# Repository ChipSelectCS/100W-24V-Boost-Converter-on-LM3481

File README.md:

# 100W-24V-Boost-Converter-on-LM3481

Great and powerful 100W Step up Converter. Provides and option to toggle the converter on and off using the onboard pins.

Open in KiCad

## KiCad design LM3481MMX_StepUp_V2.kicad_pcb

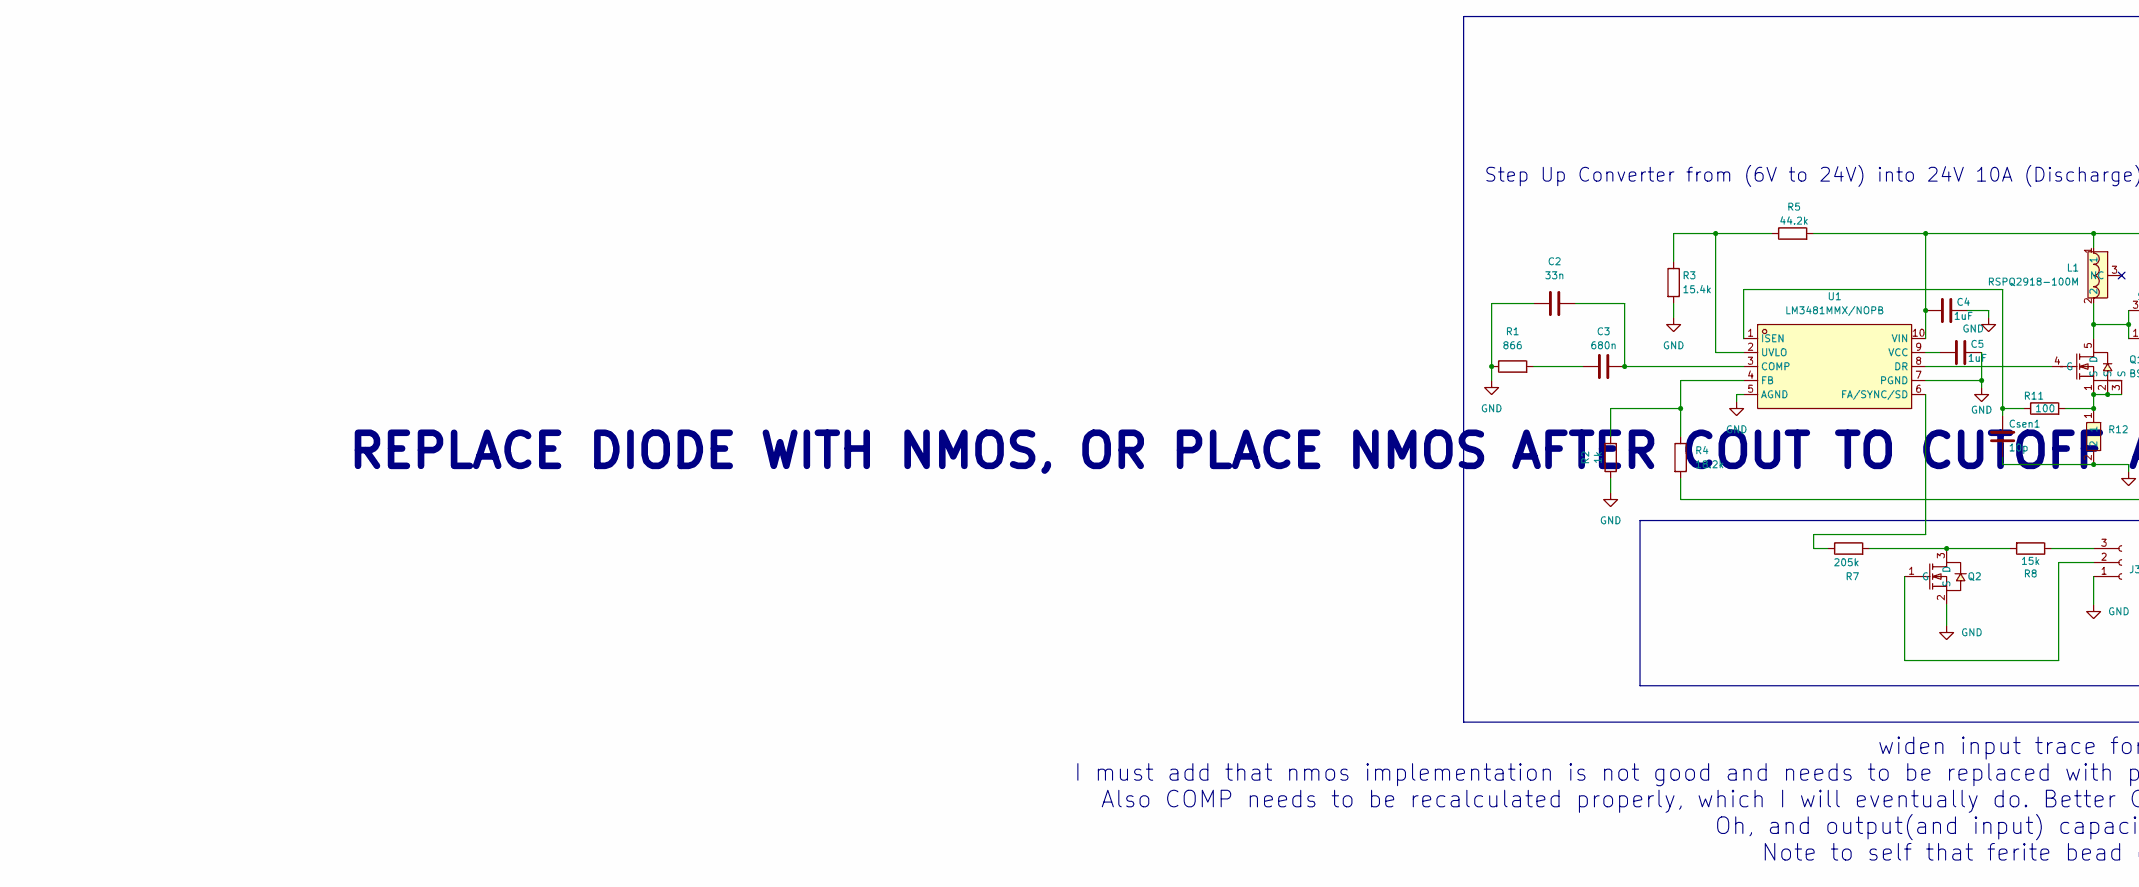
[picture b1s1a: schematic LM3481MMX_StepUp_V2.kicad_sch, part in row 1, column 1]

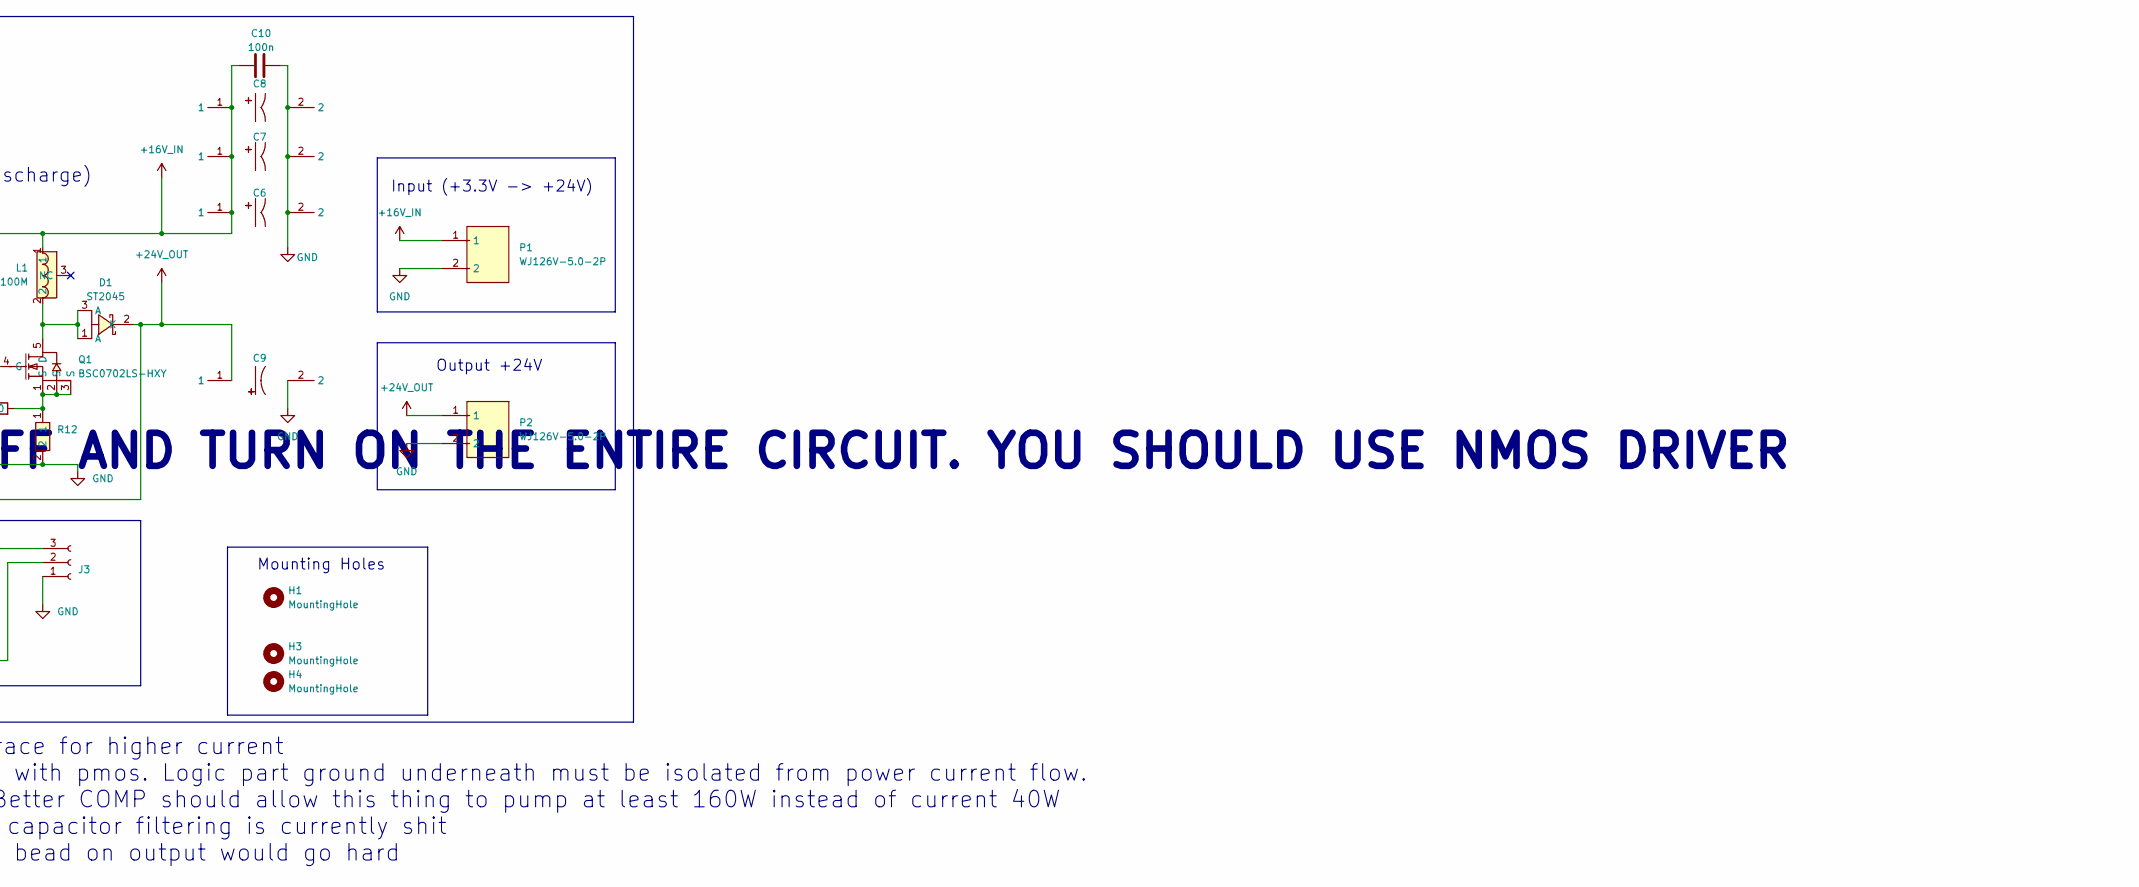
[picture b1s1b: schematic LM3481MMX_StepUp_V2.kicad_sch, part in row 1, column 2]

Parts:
C2: 33n; C_0603_1608Metric
C3: 680n; C_0603_1608Metric
C4, C5: 1uF; C_0603_1608Metric
C6, C7, C8: HV1H227M1010PZ; CAP-SMD_BD10.0-L10.3-W10.3-LS11.3-FD; LCSC Part C5246564
C9: OVZ121M1V1013-TRO; CAP-SMD_BD10.0-L10.4-W10.4-LS11.0-FD; LCSC Part C250089
C10: 100n; C_0603_1608Metric
Csen1: 10p; C_0603_1608Metric
D1: ST2045; TO-277_3P-L5.4-W4.0-LS6.5-BR; LCSC Part C840773
H1, H3, H4: MountingHole; MountingHole_2.2mm_M2
J3: Conn_01x03_Socket; PinSocket_1x03_P2.54mm_Vertical
L1: RSPQ2918-100M; IND-SMD_3P-L27.9-W19.7-P10.43-LS27.9-BL-A; LCSC Part C32712982
P1, P2: WJ126V-5.0-2P; CONN-TH_WJ126V-5.0-2P; LCSC Part C8404
Q1: BSC0702LS-HXY; TDSON-8_L5.9-W5.2-P1.27-BL; LCSC Part C20606289
Q2: 2N7002K_C414015; SOT-23-3_L2.9-W1.3-P1.90-LS2.4-BR; LCSC Part C414015
R1: 866; R_0603_1608Metric
R2: 1k; R_0603_1608Metric
R3: 15.4k; R_0603_1608Metric
R4: 18.2k; R_0603_1608Metric
R5: 44.2k; R_0603_1608Metric
R7: 205k; R_0603_1608Metric
R8: 15k; R_0603_1608Metric
R11: 100; R_0603_1608Metric
R12: FRM252WFR0025TN; R2512; LCSC Part C7420002
U1: LM3481MMX/NOPB; VSSOP-10_L3.0-W3.0-P0.50-LS4.9-BL; LCSC Part C543002

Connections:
+16V_IN: C4.1, C6.1, C7.1, C8.1, C10.2, L1.1, P1.1, R5.2, U1.10 (VIN)
+24V_OUT: C9.1, D1.2 (K), P2.1, R4.2
GND: C2.1, C4.2, C5.2, C6.2, C7.2, C8.2, C9.2, C10.1, Csen1.1, J3.1, P1.2, P2.2, Q2.2 (S), R1.1, R2.1, R3.2, R12.2, U1.5 (AGND), U1.7 (PGND)
unnamed: C3.1, R1.2
unnamed: J3.2, Q2.1 (G)
unnamed: J3.3, R8.1
unnamed: D1.1 (A), D1.3 (A), L1.2, Q1.5 (D)
unnamed: Q1.4 (G), U1.8 (DR)
unnamed: Q1.1 (S), Q1.2 (S), Q1.3 (S), R11.2, R12.1
unnamed: Q2.3 (D), R7.2, R8.2
unnamed: C2.2, C3.2, U1.3 (COMP)
unnamed: R7.1, U1.6 (FA/SYNC/SD)
unnamed: R2.2, R4.1, U1.4 (FB)
unnamed: Csen1.2, R11.1, U1.1 (ISEN)
unnamed: R3.1, R5.1, U1.2 (UVLO)
unnamed: C5.1, U1.9 (VCC)

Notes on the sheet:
REPLACE DIODE WITH NMOS, OR PLACE NMOS AFTER COUT TO CUTOFF AND TURN ON THE ENTIRE CIRCUIT. YOU SHOULD USE NMOS DRIVER
widen input trace for higher current I must add that nmos implementation is not good and needs to be replaced with pmos. Logic part ground underneath must be isolated from power current flow. Also COMP needs to be recalculated properly, which I will eventually do. Better COMP should allow this thin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
Input (+3.3V -> +24V)
Step Up Converter from (6V to 24V) into 24V 10A (Discharge)
Output +24V
Mounting Holes

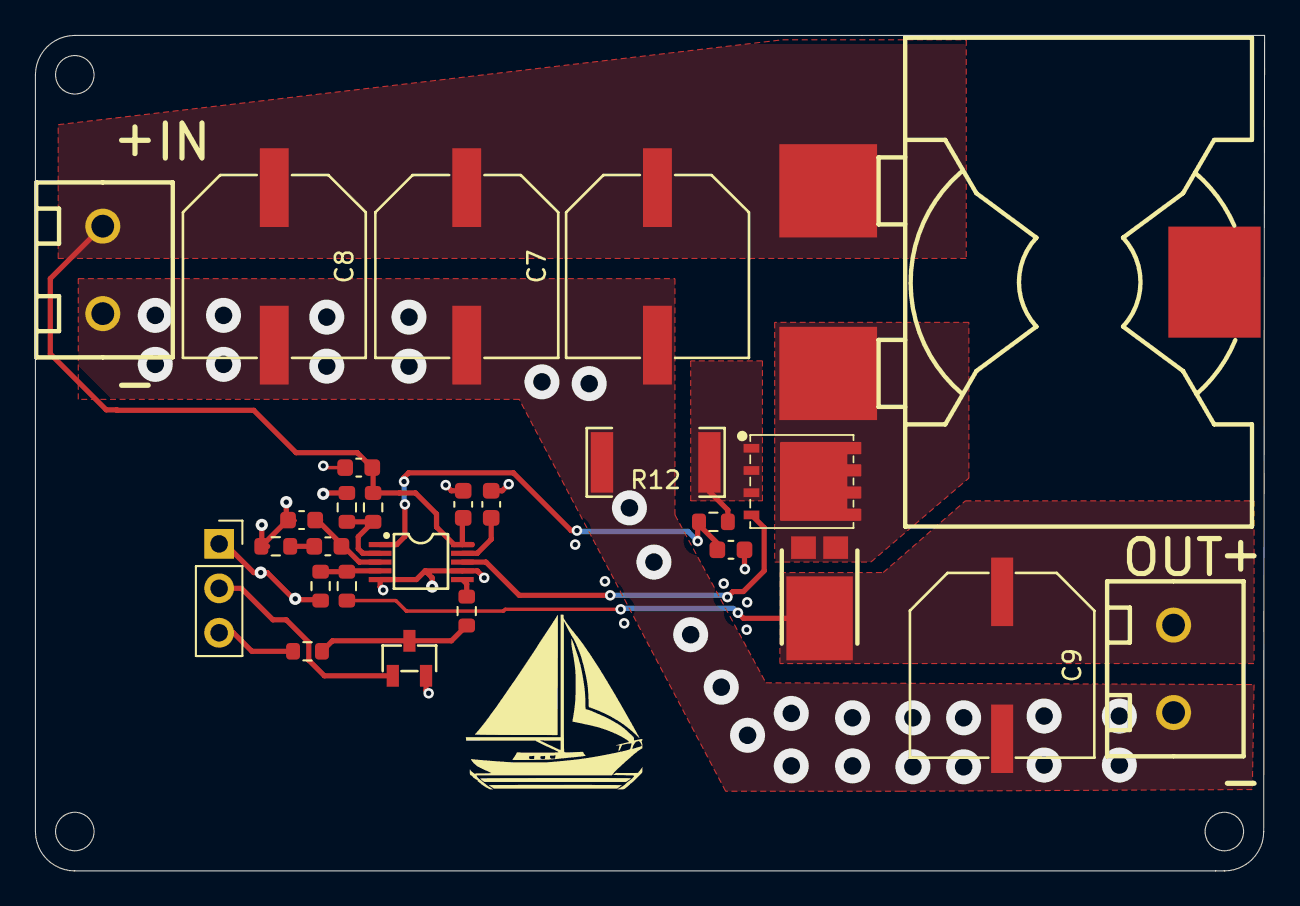
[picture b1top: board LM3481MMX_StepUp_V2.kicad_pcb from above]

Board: 2 copper layers, 70.3 x 47.8 mm, 30 parts (0 on the bottom side), 16 nets.

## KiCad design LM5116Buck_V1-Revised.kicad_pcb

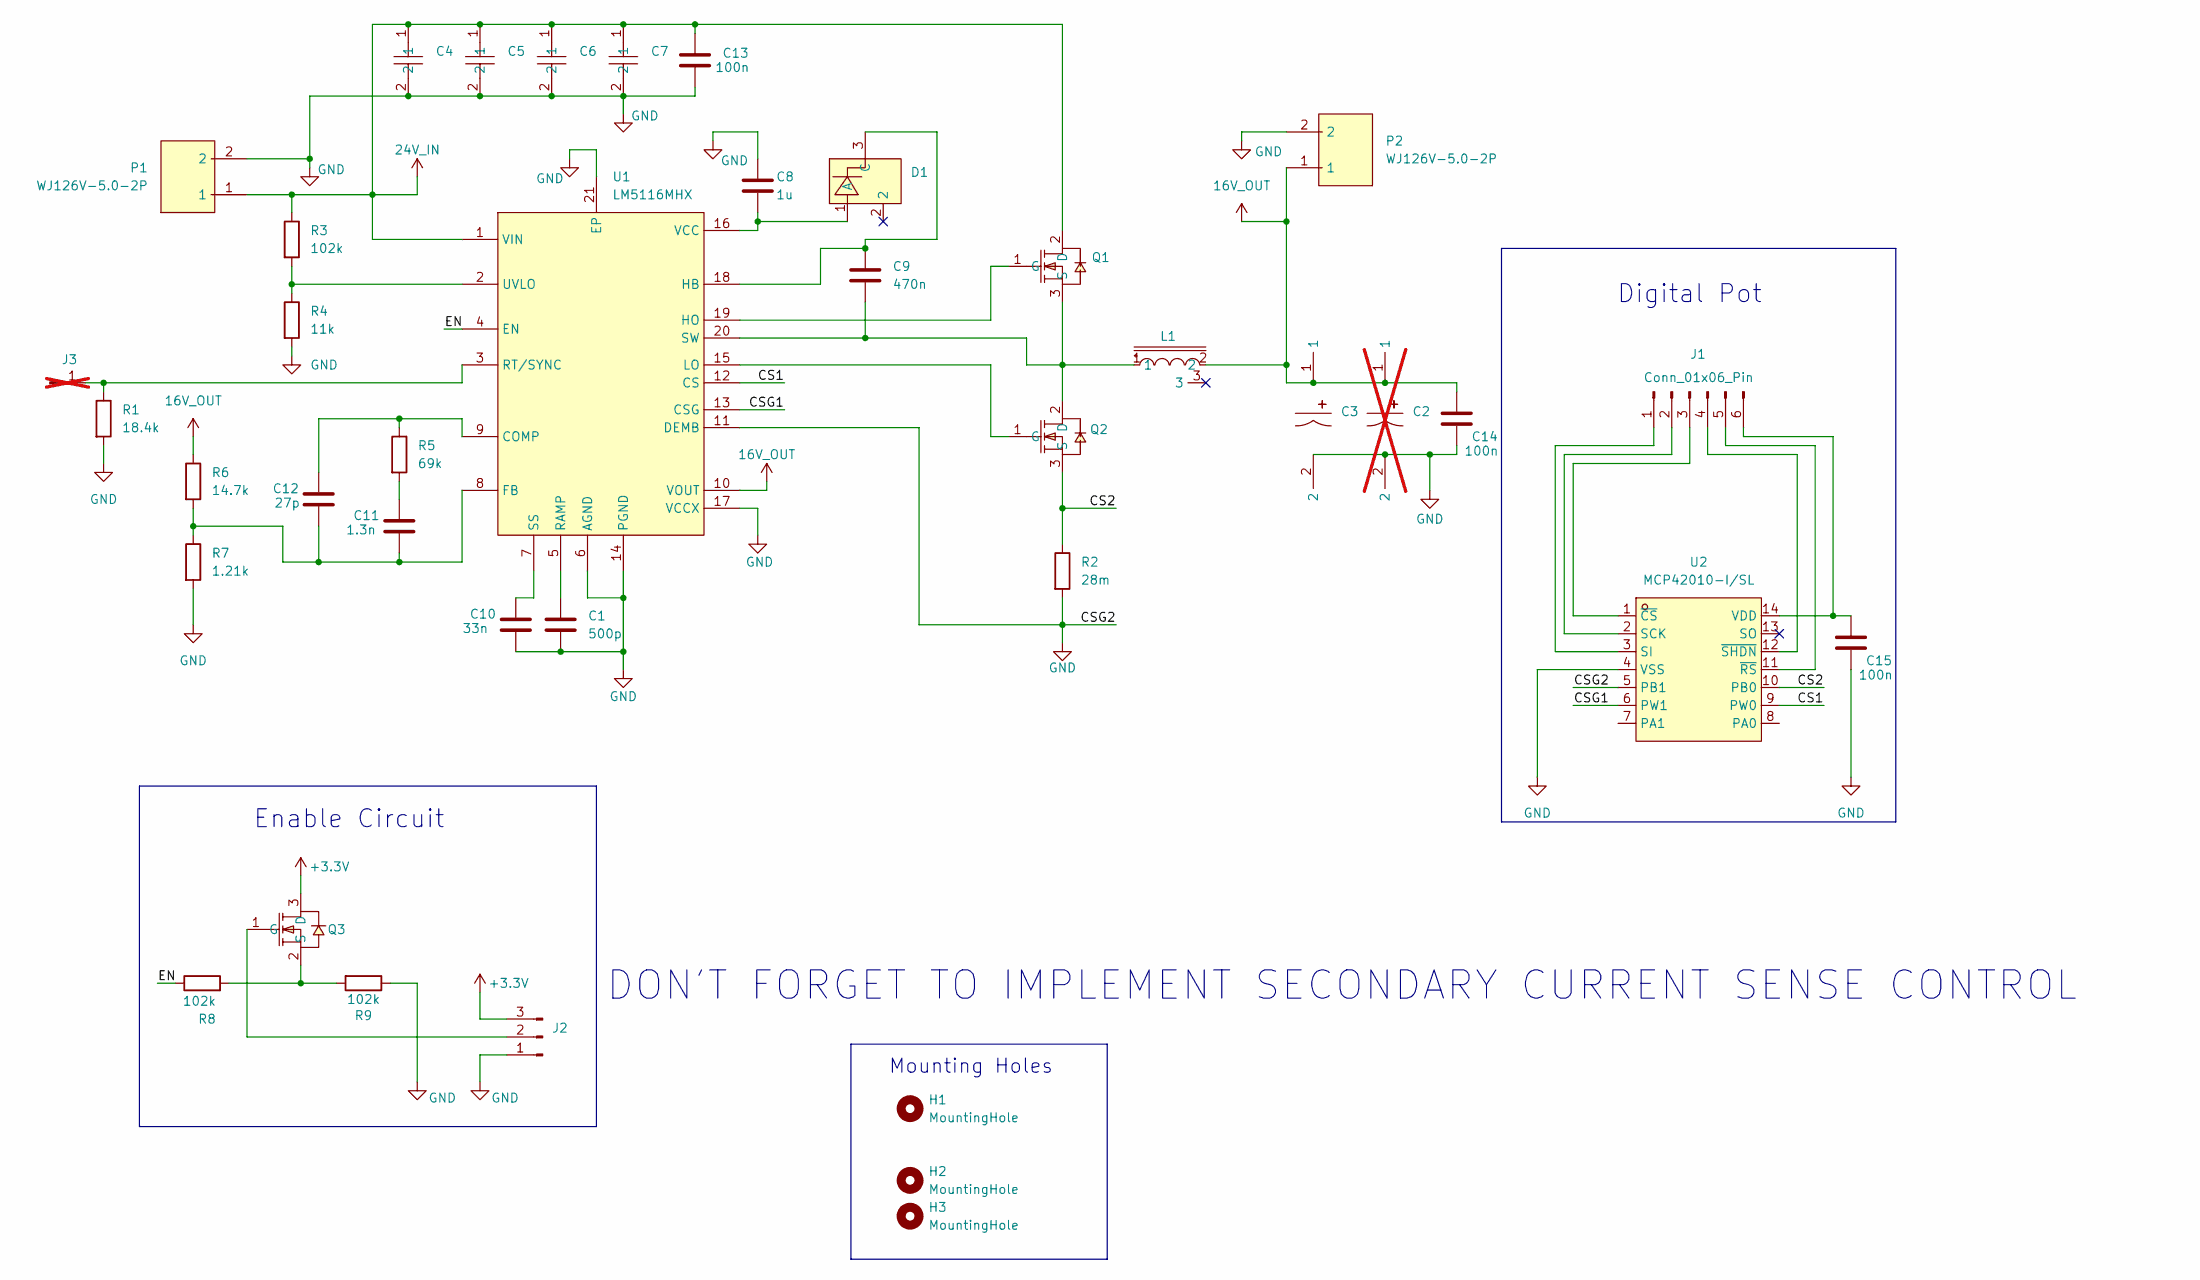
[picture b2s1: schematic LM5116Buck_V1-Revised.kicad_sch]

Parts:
C1: 500p; C_0603_1608Metric
C2: HV1H227M1010PZ; CAP-SMD_BD10.0-L10.3-W10.3-LS11.3-FD; LCSC Part C5246564; not fitted
C3: HV1H227M1010PZ; CAP-SMD_BD10.0-L10.3-W10.3-LS11.3-FD; LCSC Part C5246564
C4, C5, C6, C7: FS32X225K101EGG; C1210; LCSC Part C153036
C8: 1u; C_0603_1608Metric
C9: 470n; C_0603_1608Metric
C10: 33n; C_0603_1608Metric
C11: 1.3n; C_0603_1608Metric
C12: 27p; C_0603_1608Metric
C13, C14, C15: 100n; C_0603_1608Metric
D1: BAS20LT1G; SOT-23-3_L2.9-W1.3-P1.90-LS2.4-BL-1; LCSC Part C232529
H1, H2, H3: MountingHole; MountingHole_2.2mm_M2
J1: Conn_01x06_Pin; PinHeader_1x06_P2.54mm_Vertical
J2: Conn_01x03_Pin; PinHeader_1x03_P2.54mm_Vertical
J3: Conn_01x01_Pin; PinHeader_1x01_P2.54mm_Vertical; not fitted
L1: FC-SE2918-220M; IND-SMD_3P-L27.9-W19.7-P10.43-LS27.9-BL-A; LCSC Part C2962789
P1, P2: WJ126V-5.0-2P; CONN-TH_WJ126V-5.0-2P; LCSC Part C8404
Q1, Q2: IRFR1205TRPBF-ES; TO-252-2_L6.6-W6.1-P4.57-LS9.9-BR-CW; LCSC Part C21713850
Q3: 2N7002K_C414015; SOT-23-3_L2.9-W1.3-P1.90-LS2.4-BR; LCSC Part C414015
R1: 18.4k; R_0603_1608Metric
R2: 28m; R_2512_6332Metric
R3, R8, R9: 102k; R_0603_1608Metric
R4: 11k; R_0603_1608Metric
R5: 69k; R_0603_1608Metric
R6: 14.7k; R_0603_1608Metric
R7: 1.21k; R_0603_1608Metric
U1: LM5116MHX; HTSSOP-20_L6.5-W4.4-P0.65-LS6.4-BL-EP; LCSC Part C13755
U2: MCP42010-I/SL; SOIC-14_L8.7-W3.9-P1.27-LS6.0-BL; LCSC Part C481366

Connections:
16V_OUT: C2.1, C3.1, C14.1, L1.2, P2.1, R6.1, U1.10 (VOUT)
24V_IN: C4.1, C5.1, C6.1, C7.1, C13.1, P1.1, Q1.2 (D), R3.1, U1.1 (VIN)
+3.3V: J2.3, Q3.3 (D)
/CS1: U1.12 (CS), U2.9 (PW0)
/CS2: Q2.3 (S), R2.1, U2.10 (PB0)
/CSG1: U1.13 (CSG), U2.6 (PW1)
/EN: R8.1, U1.4 (EN)
GND: C1.2, C2.2, C3.2, C4.2, C5.2, C6.2, C7.2, C8.1, C10.2, C13.2, C14.2, C15.2, J2.1, P1.2, P2.2, R1.2, R2.2, R4.2, R7.2, R9.1, U1.6 (AGND), U1.11 (DEMB), U1.14 (PGND), U1.17 (VCCX), U1.21 (EP), U1.GND, U2.4 (VSS), U2.5 (PB1)
unnamed: C11.1, R5.2
unnamed: C8.2, D1.1 (A), U1.16 (VCC)
unnamed: C9.1, D1.3 (C), U1.18 (HB)
unnamed: J1.1, U2.3 (SI)
unnamed: J1.2, U2.2 (SCK)
unnamed: J1.3, U2.1 (~CS)
unnamed: J1.4, U2.12 (~SHDN)
unnamed: J1.5, U2.11 (~RS)
unnamed: C15.1, J1.6, U2.14 (VDD)
unnamed: J2.2, Q3.1 (G)
unnamed: J3.1, R1.1, U1.3 (RT/SYNC)
unnamed: Q1.1 (G), U1.19 (HO)
unnamed: C9.2, L1.1, Q1.3 (S), Q2.2 (D), U1.20 (SW)
unnamed: Q2.1 (G), U1.15 (LO)
unnamed: Q3.2 (S), R8.2, R9.2
unnamed: C12.1, R5.1, U1.9 (COMP)
unnamed: C11.2, C12.2, R6.2, R7.1, U1.8 (FB)
unnamed: C1.1, U1.5 (RAMP)
unnamed: C10.1, U1.7 (SS)
unnamed: R3.2, R4.1, U1.2 (UVLO)

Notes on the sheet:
Enable Circuit
Digital Pot
DON'T FORGET TO IMPLEMENT SECONDARY CURRENT SENSE CONTROL
Mounting Holes

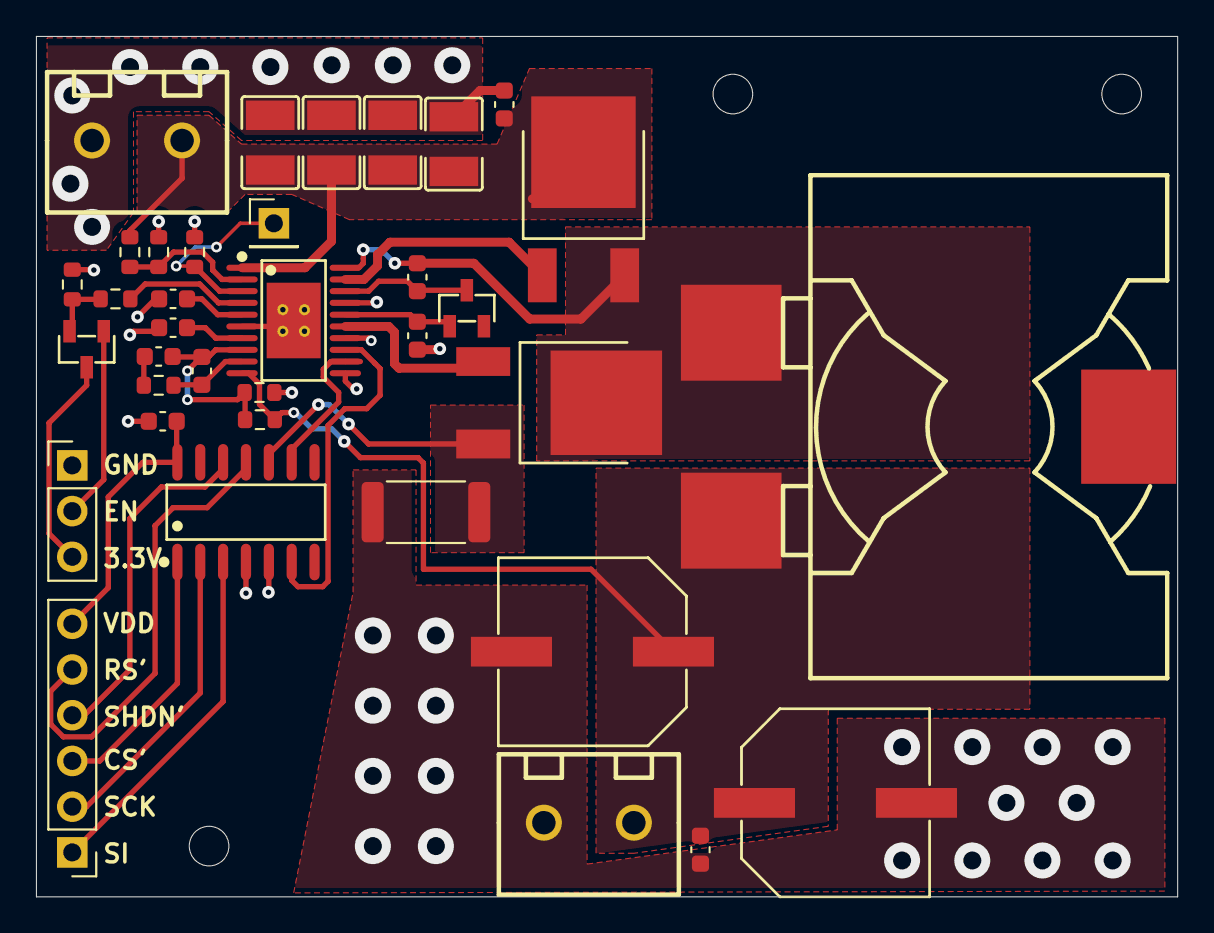
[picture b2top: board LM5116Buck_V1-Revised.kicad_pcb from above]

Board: 2 copper layers, 63.4 x 47.8 mm, 39 parts (0 on the bottom side), 28 nets.

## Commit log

2025-09-17 first upload
2025-09-17 main upload
2025-09-17 image
